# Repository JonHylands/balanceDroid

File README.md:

# balanceDroid
A simple and very small 2-wheel balancing robot

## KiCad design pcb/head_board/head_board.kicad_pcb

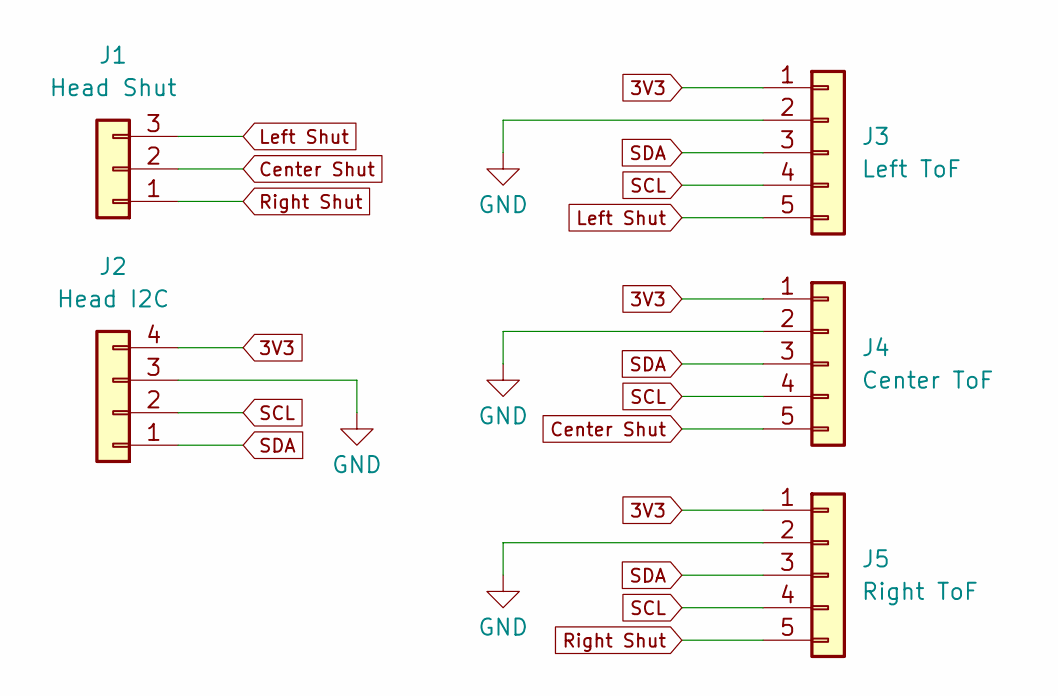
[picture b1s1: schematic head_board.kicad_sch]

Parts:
J1: Head Shut; Hirose_DF13-03P-1.25DSA_1x03_P1.25mm_Vertical
J2: Head I2C; Hirose_DF13-04P-1.25DSA_1x04_P1.25mm_Vertical
J3: Left ToF; Hirose_DF13-05P-1.25DSA_1x05_P1.25mm_Vertical
J4: Center ToF; Hirose_DF13-05P-1.25DSA_1x05_P1.25mm_Vertical
J5: Right ToF; Hirose_DF13-05P-1.25DSA_1x05_P1.25mm_Vertical

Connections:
3V3: J2.4, J3.1, J4.1, J5.1
Center Shut: J1.2, J4.5
GND: J2.3, J3.2, J4.2, J5.2
Left Shut: J1.3, J3.5
Right Shut: J1.1, J5.5
SCL: J2.2, J3.4, J4.4, J5.4
SDA: J2.1, J3.3, J4.3, J5.3

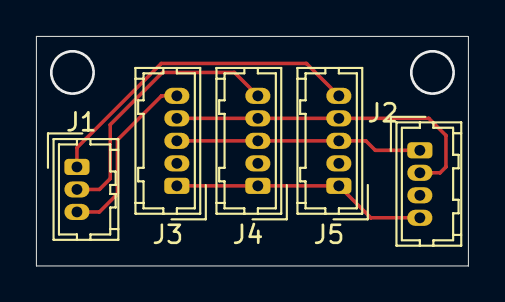
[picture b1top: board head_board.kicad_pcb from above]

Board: 2 copper layers, 24.0 x 12.8 mm, 5 parts (0 on the bottom side), 7 nets.

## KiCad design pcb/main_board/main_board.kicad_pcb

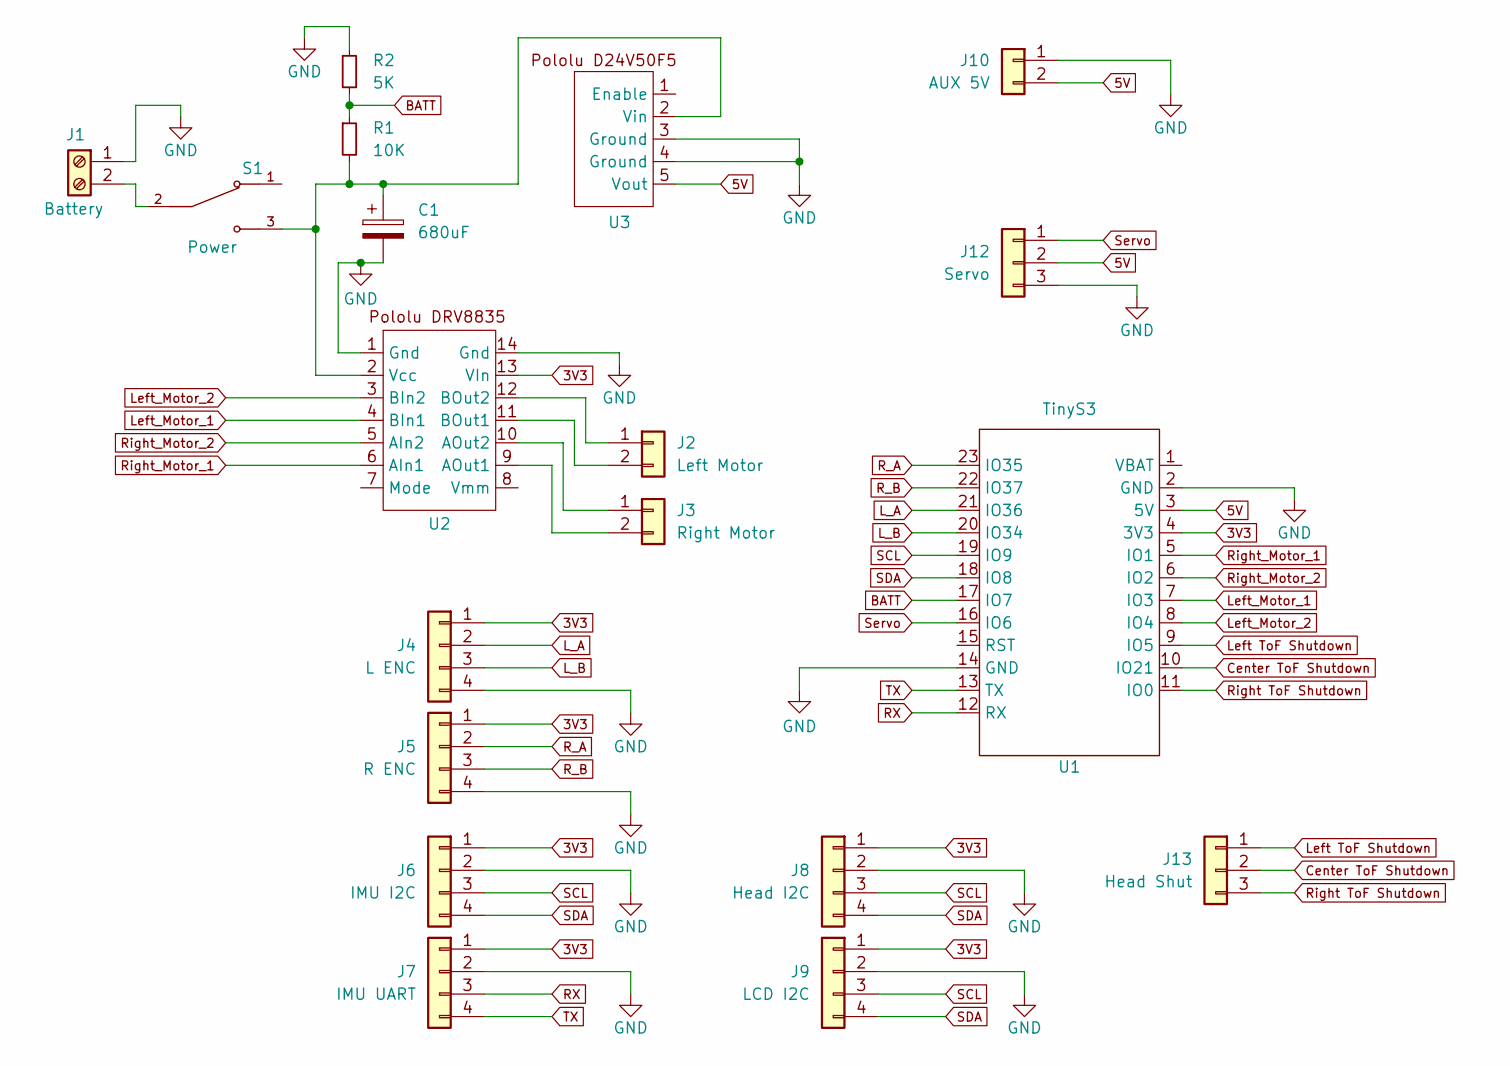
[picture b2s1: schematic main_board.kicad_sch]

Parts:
C1: 680uF; CP_Radial_D8.0mm_P3.50mm
J1: Battery; Molex_SPOX_5267-02A_1x02_P2.50mm_Vertical
J2: Left Motor; Molex_SPOX_5267-02A_1x02_P2.50mm_Vertical
J3: Right Motor; Molex_SPOX_5267-02A_1x02_P2.50mm_Vertical
J4: L ENC; Hirose_DF13-04P-1.25DSA_1x04_P1.25mm_Vertical
J5: R ENC; Hirose_DF13-04P-1.25DSA_1x04_P1.25mm_Vertical
J6: IMU I2C; Hirose_DF13-04P-1.25DSA_1x04_P1.25mm_Vertical
J7: IMU UART; Hirose_DF13-04P-1.25DSA_1x04_P1.25mm_Vertical
J8: Head I2C; Hirose_DF13-04P-1.25DSA_1x04_P1.25mm_Vertical
J9: LCD I2C; PinSocket_1x04_P2.54mm_Horizontal
J10: AUX 5V; Molex_SPOX_5267-02A_1x02_P2.50mm_Vertical
J12: Servo; PinHeader_1x03_P2.54mm_Vertical
J13: Head Shut; Hirose_DF13-03P-1.25DSA_1x03_P1.25mm_Vertical
R1: 10K; R_0603_1608Metric
R2: 5K; R_0603_1608Metric
S1: Power; Slide Switch 5A; PARTREV D
U1: TinyS3
U2: DIP-14_W7.62mm_LongPads
U3: PinHeader_1x05_P2.54mm_Vertical

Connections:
3V3: J4.1, J5.1, J6.1, J7.1, J8.1, J9.1, U1.4 (3V3), U2.13 (VIn)
5V: J10.2, J12.2, U1.3 (5V), U3.5 (Vout)
BATT: R1.1, R2.2, U1.17 (IO7)
Center ToF Shutdown: J13.2, U1.10 (IO21)
GND: C1.2, J1.1, J4.4, J5.4, J6.2, J7.2, J8.2, J9.2, J10.1, J12.3, R2.1, U1.2 (GND), U1.14 (GND), U2.1 (Gnd), U2.14 (Gnd), U3.3 (Ground), U3.4 (Ground)
L_A: J4.2, U1.21 (IO36)
L_B: J4.3, U1.20 (IO34)
Left ToF Shutdown: J13.1, U1.9 (IO5)
Left_Motor_1: U1.7 (IO3), U2.4 (BIn1)
Left_Motor_2: U1.8 (IO4), U2.3 (BIn2)
unnamed: J1.2, S1.2
unnamed: J2.1, U2.12 (BOut2)
unnamed: J2.2, U2.11 (BOut1)
unnamed: J3.1, U2.10 (AOut2)
unnamed: J3.2, U2.9 (AOut1)
unnamed: C1.1, R1.2, S1.3, U2.2 (Vcc), U3.2 (Vin)
RX: J7.3, U1.12 (RX)
R_A: J5.2, U1.23 (IO35)
R_B: J5.3, U1.22 (IO37)
Right ToF Shutdown: J13.3, U1.11 (IO0)
Right_Motor_1: U1.5 (IO1), U2.6 (AIn1)
Right_Motor_2: U1.6 (IO2), U2.5 (AIn2)
SCL: J6.3, J8.3, J9.3, U1.19 (IO9)
SDA: J6.4, J8.4, J9.4, U1.18 (IO8)
Servo: J12.1, U1.16 (IO6)
TX: J7.4, U1.13 (TX)

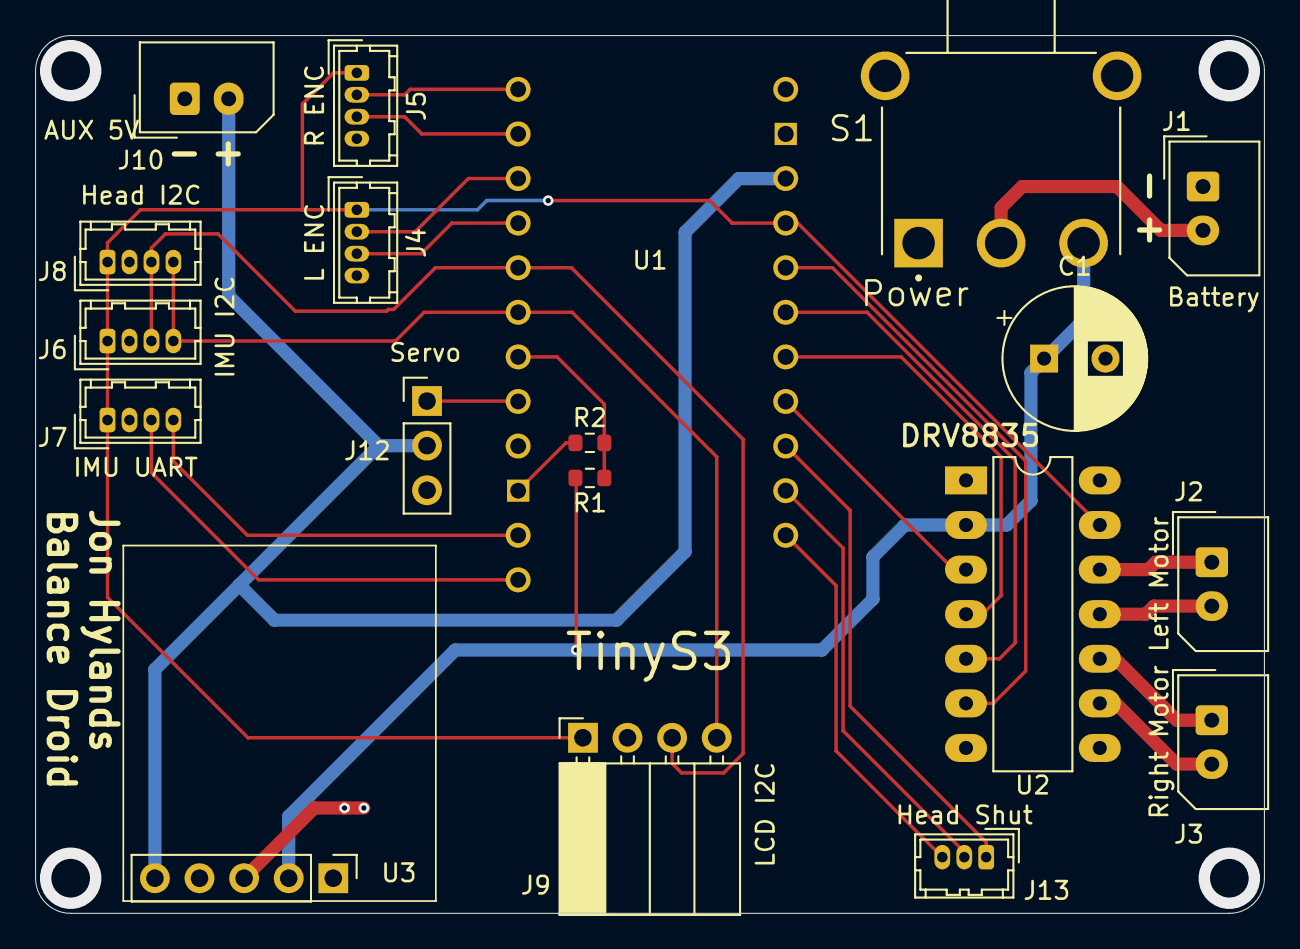
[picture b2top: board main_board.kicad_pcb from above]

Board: 2 copper layers, 70.0 x 50.0 mm, 19 parts (0 on the bottom side), 26 nets.

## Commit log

2024-06-16 First push including code, PCB design, etc
2024-06-16 Fixed render
